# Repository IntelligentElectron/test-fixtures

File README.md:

# test-fixtures

Small, curated, **redistributable** EDA design files used as shared test fixtures
by IntelligentElectron's tooling. This repo is public and meant to be cloned /
submoduled by other repos' CI.

## Who uses it

- **[universal-netlist](https://github.com/IntelligentElectron/universal-netlist)** —
  consumes this repo as a git submodule at `test/fixtures` for parser/connectivity tests
  (Altium + Cadence today; KiCad parser in development).
- **[pcb-lens](https://github.com/IntelligentElectron/pcb-lens)** —
  consumes this repo as a git submodule at `test/fixtures`; runs
  `ipc2581/download-fixtures.sh` to fetch the IPC-2581 boards for layout tests.

## Layout

| Dir | Contents |
|-----|----------|
| `kicad/` | 13 KiCad projects, deliberately spanning **flat → deep hierarchy**, simple → complex, with **buses / global & hierarchical labels / power symbols** — chosen to exercise a KiCad parser. |
| `altium/` | Altium `.PrjPcb` / `.SchDoc` designs. |
| `cadence/` | Cadence Allegro / CIS designs (incl. exported `.dat` netlists). |
| `ipc2581/` | IPC-2581 PCB layout boards (RevA/B/C). Large XML downloaded on demand via `ipc2581/download-fixtures.sh` — not committed. |
| `NOTICE.md` | Upstream source, license, and copyright for every fixture. |

The `kicad/` set ranges from a single-sheet baseline (no hierarchy) up to 24-sheet,
depth-5 hierarchical designs with hundreds of bus connections — so a parser that
handles these handles the long tail.

## Using it from another repo

```sh
git submodule add https://github.com/IntelligentElectron/test-fixtures test/fixtures
git submodule update --init --remote      # pull latest fixtures
```

In CI (`actions/checkout`), set `submodules: true`. The repo is public, so the default
`GITHUB_TOKEN` can clone it — no extra credentials needed.

## Licensing

Every fixture is open-source / open-hardware (permissive or OSHW licenses) and is
**redistributable with attribution**; see `NOTICE.md`. If you are a copyright holder and
want your files removed, please open an issue.

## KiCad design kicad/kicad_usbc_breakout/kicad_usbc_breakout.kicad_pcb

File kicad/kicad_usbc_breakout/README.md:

# KiCad USB-C Breakout Board

Breaks out the USB 2.0 signals of a USB-C connector: VBUS, GND, D+, D- to pads
for soldering wires.

See the [schematic](kicad_usbc_breakout_schematic.pdf),
[pcb](kicad_usbc_breakout_pcb.pdf), and [BOM](usbc_breakout_BOM.csv).

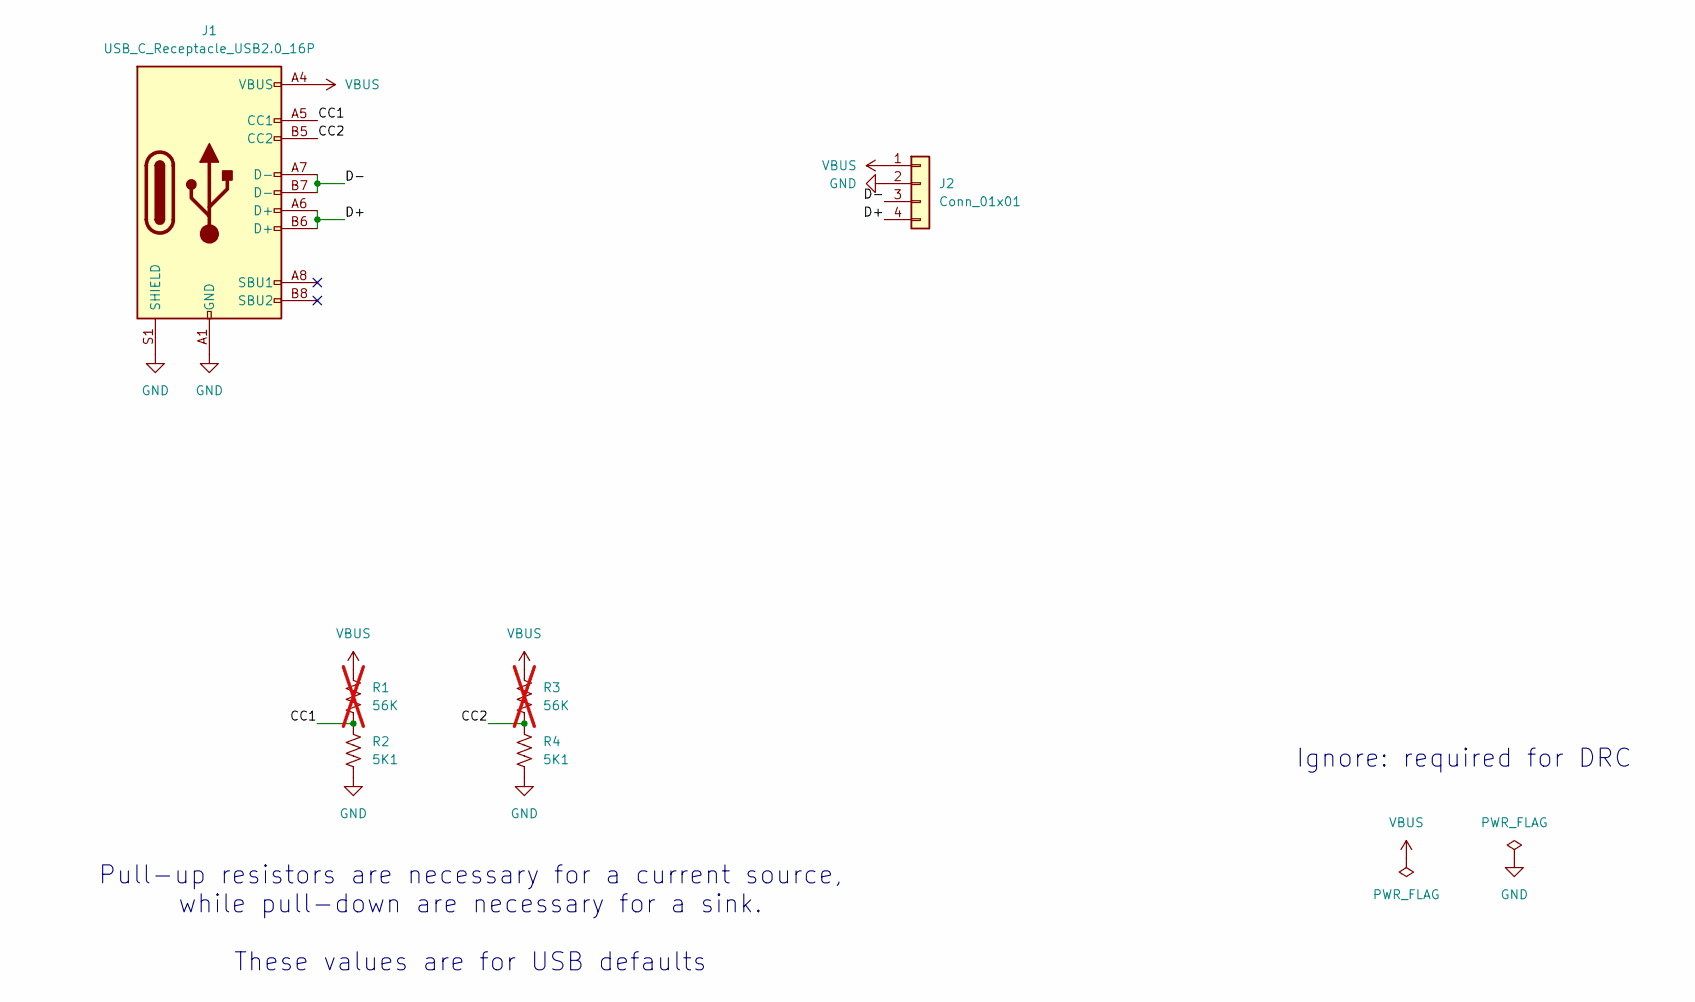
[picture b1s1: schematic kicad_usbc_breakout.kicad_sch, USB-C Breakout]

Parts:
J1: USB_C_Receptacle_USB2.0_16P; USB_C_Receptacle_GCT_USB4085_Reduced_Pad_Size; MFR Part Num USB4085-GF-A
J2: Conn_01x01; SolderWire-0.5sqmm_1x04_P4.8mm_D0.9mm_OD2.3mm_Relief
R1, R3: 56K; R_0805_2012Metric_Pad1.20x1.40mm_HandSolder; MFR Part Num CRCW080556K0FKEA; not fitted
R2, R4: 5K1; R_0805_2012Metric_Pad1.20x1.40mm_HandSolder; MFR Part Num CRCW08055K10FKEA

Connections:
/CC1: J1.A5 (CC1), R1.2, R2.1
/CC2: J1.B5 (CC2), R3.2, R4.1
/D+: J1.A6 (D+), J1.B6 (D+), J2.4
/D-: J1.A7 (D-), J1.B7 (D-), J2.3
GND: J1.A1 (GND), J1.A12 (GND), J1.B1 (GND), J1.B12 (GND), J1.S1 (SHIELD), J2.2, R2.2, R4.2
VBUS: J1.A4 (VBUS), J1.A9 (VBUS), J1.B4 (VBUS), J1.B9 (VBUS), J2.1, R1.1, R3.1

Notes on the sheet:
Pull-up resistors are necessary for a current source, while pull-down are necessary for a sink. These values are for USB defaults
Ignore: required for DRC

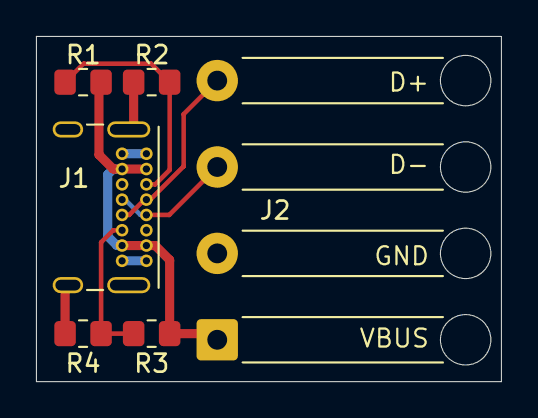
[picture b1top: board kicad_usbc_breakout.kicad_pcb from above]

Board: 2 copper layers, 25.8 x 19.2 mm, 6 parts (0 on the bottom side), 6 nets.

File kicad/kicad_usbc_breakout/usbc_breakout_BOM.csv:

"Reference","Value","Datasheet","Footprint","Qty","DNP","MFR","MFR Part Num"
"J1","USB_C_Receptacle_USB2.0_16P","https://www.usb.org/sites/default/files/documents/usb_type-c.zip","AAAA_Project_Library:USB_C_Receptacle_GCT_USB4085_Reduced_Pad_Size","1","","GCT","USB4085-GF-A"
"J2","Conn_01x01","~","Connector_Wire:SolderWire-0.5sqmm_1x04_P4.8mm_D0.9mm_OD2.3mm_Relief","1","","",""
"R1,R3","56K","~","Resistor_SMD:R_0805_2012Metric_Pad1.20x1.40mm_HandSolder","2","DNP","Vishay","CRCW080556K0FKEA"
"R2,R4","5K1","~","Resistor_SMD:R_0805_2012Metric_Pad1.20x1.40mm_HandSolder","2","","Vishay","CRCW08055K10FKEA"

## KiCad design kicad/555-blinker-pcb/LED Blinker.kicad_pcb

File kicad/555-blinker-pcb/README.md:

# LED Blinker Circuit with 555 Timer

This is a simple PCB designed in Kicad 7 for blinking an LED using an NA555P IC 555 timer. 

Below are screenshots of the PCB:

Schematics:

PCB Layout:

3D view of PCB:

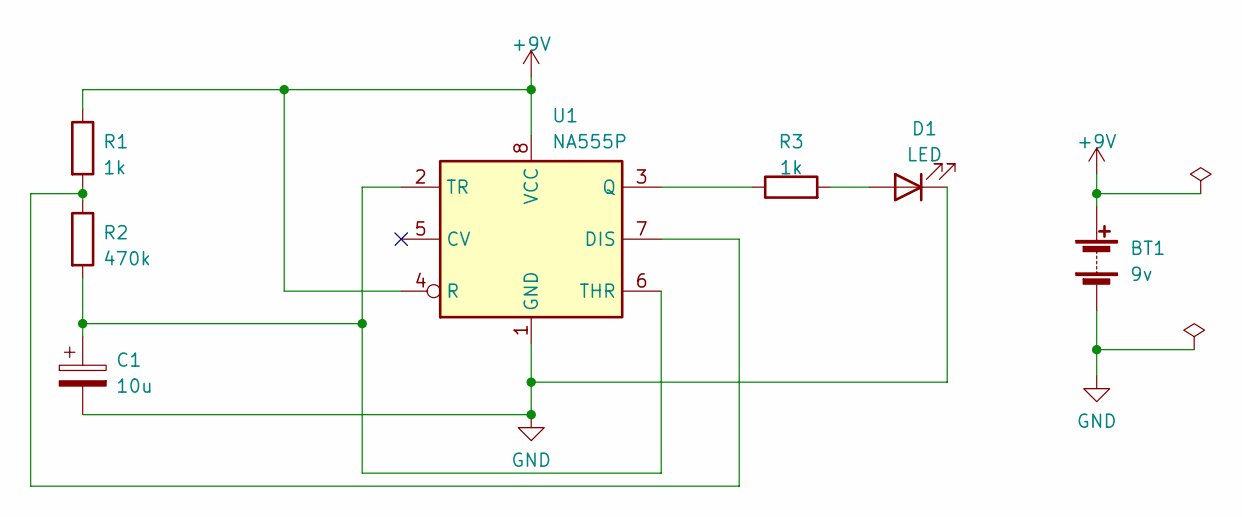
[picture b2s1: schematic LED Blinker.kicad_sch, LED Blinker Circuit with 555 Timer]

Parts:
BT1: 9v; TerminalBlock_bornier-2_P5.08mm
C1: 10u; CP_Axial_L10.0mm_D4.5mm_P15.00mm_Horizontal
D1: LED; LED_D8.0mm
R1, R3: 1k; R_Axial_DIN0204_L3.6mm_D1.6mm_P5.08mm_Horizontal
R2: 470k; R_Axial_DIN0204_L3.6mm_D1.6mm_P5.08mm_Horizontal
U1: NA555P; DIP-8_W7.62mm

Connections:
+9V: BT1.1 (+), R1.1, U1.4 (R), U1.8 (VCC)
GND: BT1.2 (-), C1.2, D1.1 (K), U1.1 (GND)
unnamed: D1.2 (A), R3.2
unnamed: R1.2, R2.1, U1.7 (DIS)
unnamed: R3.1, U1.3 (Q)
unnamed: C1.1, R2.2, U1.2 (TR), U1.6 (THR)

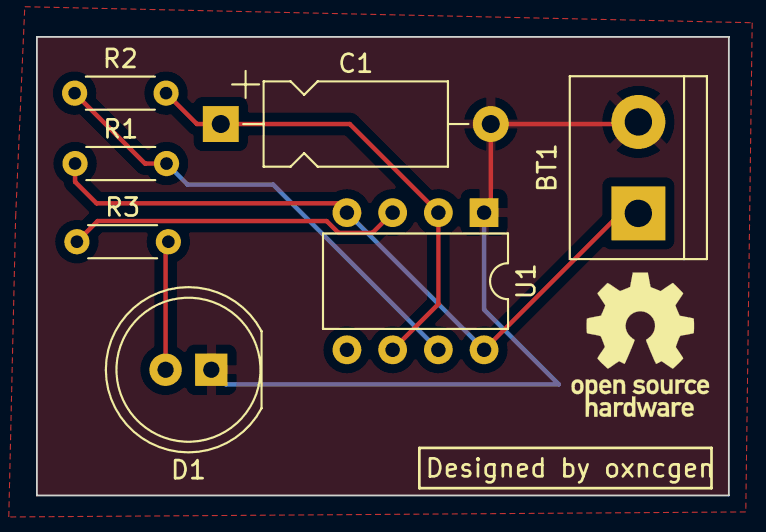
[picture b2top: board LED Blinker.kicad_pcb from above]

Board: 2 copper layers, 38.4 x 25.5 mm, 7 parts (0 on the bottom side), 6 nets.

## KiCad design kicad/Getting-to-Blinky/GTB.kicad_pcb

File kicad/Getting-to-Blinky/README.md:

# Getting To Blinky

In this project, I design a flashing LED circuit using a 555 timer. The purpose of this project is to familiarize myself with simple PCB design. The inspiration for this project comes from [Getting to Blinky 4.0](https://contextualelectronics.com/courses/getting-to-blinky/) for which I followed the tutorials in order to build my project.

## Getting Started

Simply clone the repo or download the .zip file.

### Prerequisites

To open any of the PCB design files, you will need Kicad.

### Installing

A step by step series of examples that tell you have to get a development env running

Installing Kicad

```
Kicad is free and open source and may be downloaded from http://kicad-pcb.org/download/
```

## Built With

* [Kicad](http://kicad-pcb.org/) - The PCB design software used

## Authors

* **Paul Natarajan** - *Hobbyist* - [Paul Natarajan](https://github.com/pdnataraj)
* **Contextual Electronics** - *Initial Work/Inspiration* - [Contextual Electronics](https://contextualelectronics.com/courses/getting-to-blinky/)

## License

This project is licensed under the MIT License - see the [LICENSE.md](LICENSE.md) file for details

## Acknowledgments

* Thank you Contextual Electronics for helping me take the first step towards PCB design.

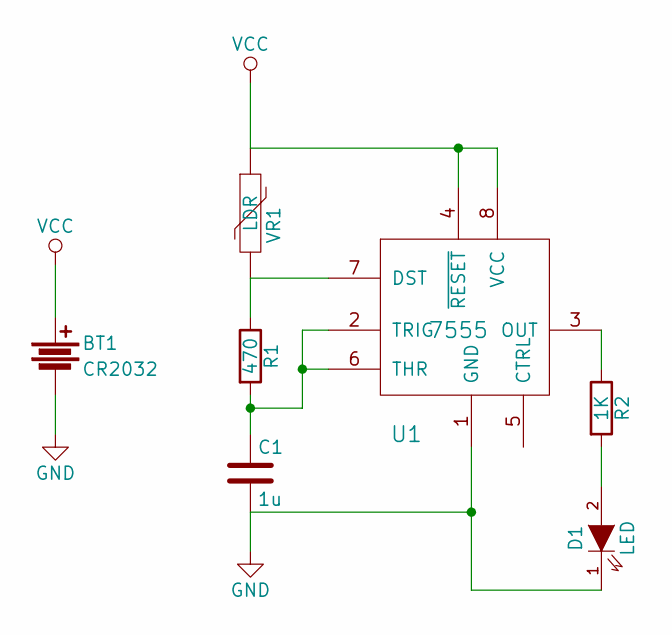
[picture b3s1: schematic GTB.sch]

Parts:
BT1: CR2032
C1: 1u; C_1206
D1: LED; LED_1206
R1: 470; R_1206
R2: 1K; R_1206
U1: 7555; SOIC-8-N
VR1: LDR; R1

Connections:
GND: BT1.2, C1.2, D1.1 (K), U1.1 (GND)
unnamed: C1.1, R1.2, U1.2 (TRIG), U1.6 (THR)
unnamed: D1.2 (A), R2.2
unnamed: R1.1, U1.7 (DST), VR1.2
unnamed: R2.1, U1.3 (OUT)
VCC: BT1.1, U1.4 (~RESET), U1.8 (VCC), VR1.1

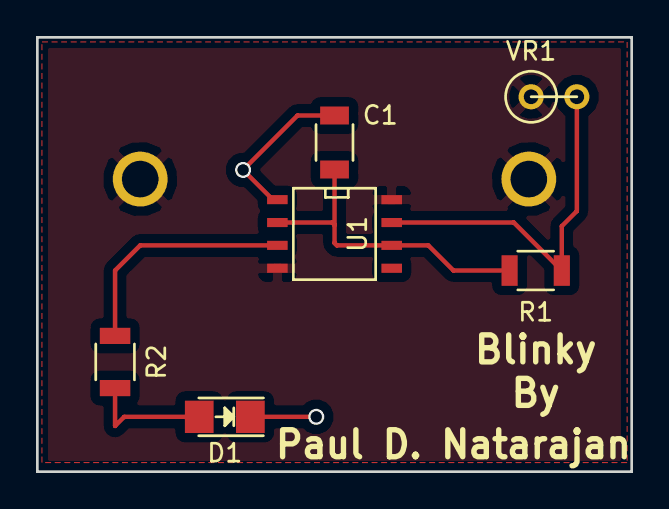
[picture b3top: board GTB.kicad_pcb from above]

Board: 2 copper layers, 33.0 x 24.1 mm, 7 parts (1 on the bottom side), 6 nets.

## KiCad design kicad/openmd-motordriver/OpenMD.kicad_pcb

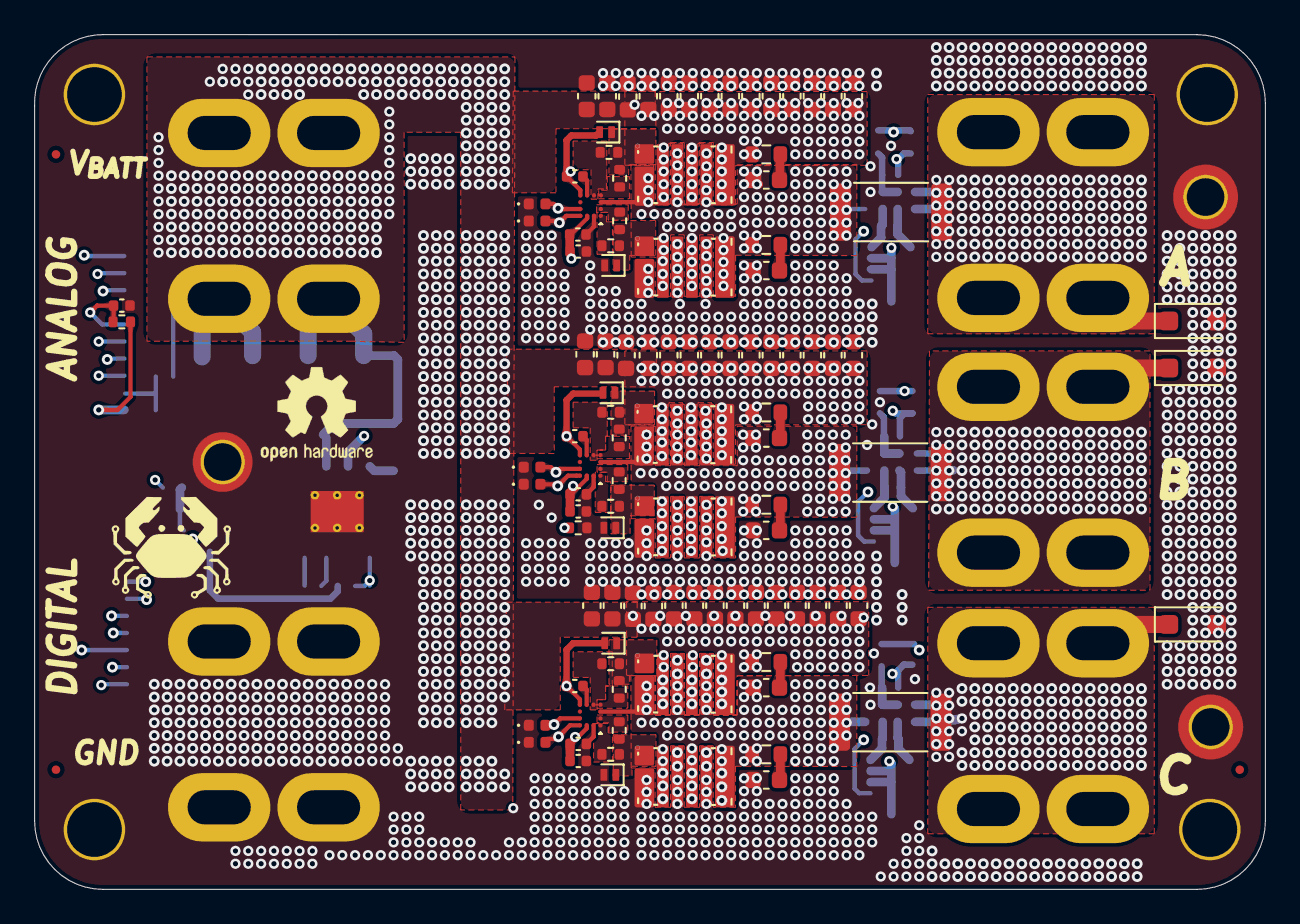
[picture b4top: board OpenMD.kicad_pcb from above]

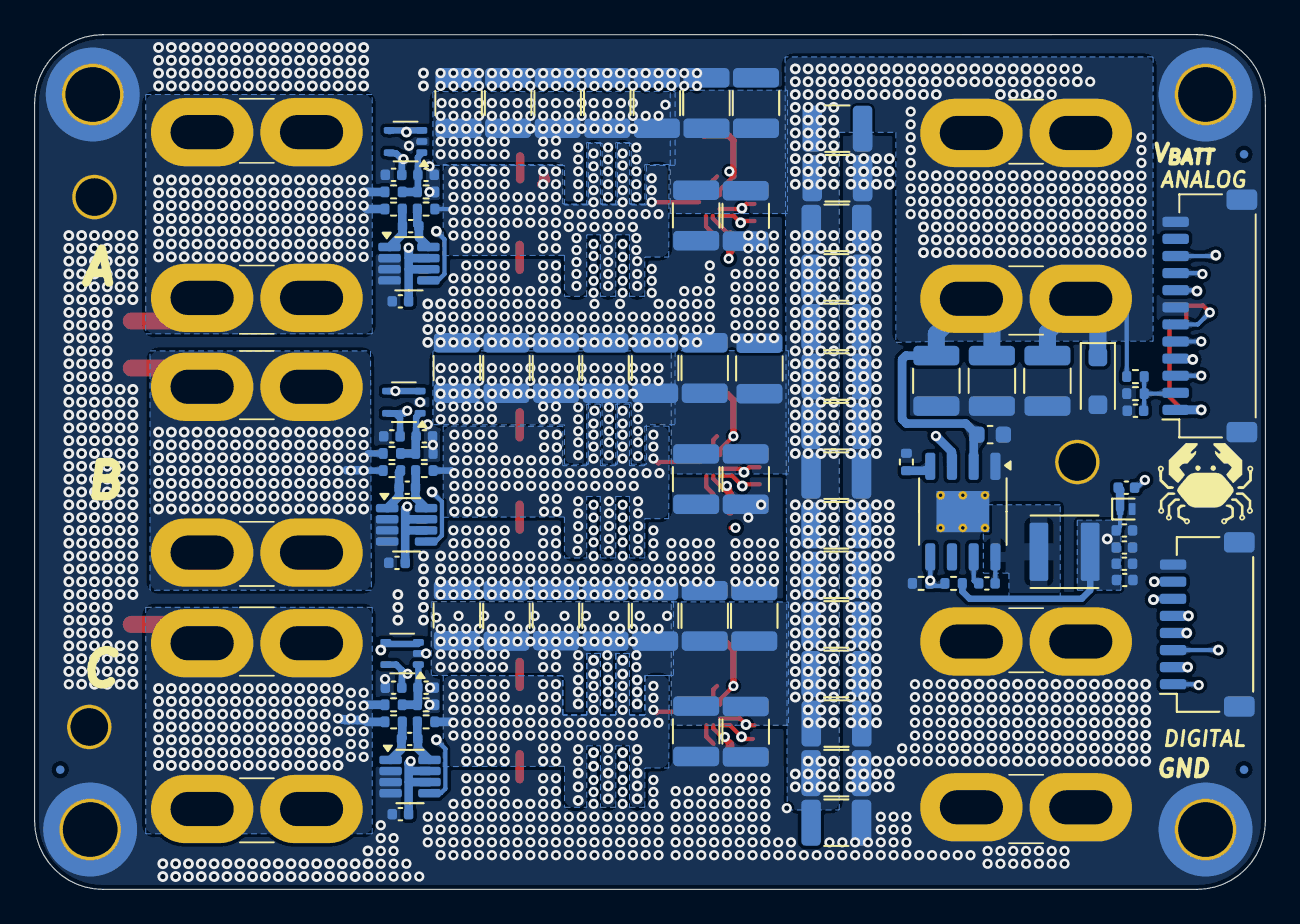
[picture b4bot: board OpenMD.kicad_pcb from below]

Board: 8 copper layers, 72.0 x 50.0 mm, 218 parts (106 on the bottom side), 65 nets.

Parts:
C1, C2, C3, C6, C7, C8, C9, C12, C15, C18, C19, C21, C23, C24, C26, C27, C28, C29, C31, C32, C34, C35, C78, C79, C80, C81, C82, C86, C87, C88, C89, C91, C93, C94, C98, C99, C100, C101, C102, C103, C104, C105, C106, C107, C108: 10uF; C_1210_3225Metric
C4, C5, C10, C13, C14, C16, C17, C20, C22, C25, C30, C33, C36, C46, C48, C50, C51, C53, C55, C58, C60, C62, C70, C71, C72, C73, C74, C75, C109, C110, C111, C112, C113, C114, C115, C116, C117, C118, C119, C120, C121, C122, C123: 100nF; C_0603_1608Metric
C11, C38, C39, C41, C42, C44, C45, C47, C52, C57, C63, C77: 100nF; C_0402_1005Metric
C37, C40, C43, C64, C65, C90: 4.7uF; C_0402_1005Metric
C49, C54, C59, C67, C68, C69, C95, C96, C97: 10nF; C_0402_1005Metric
C56, C61, C66, C83, C84, C85: C; C_0603_1608Metric
C76: 2.2nF; C_0402_1005Metric
C92: 20pF; C_0402_1005Metric
D7, D8, D9, D19: 100V; D_SOD-123F
D12, D13, D14, D15, D16, D17: 5V; D_0402_1005Metric
D18, D27, D28, D29, D30, D31, D32: 6V; D_SOD-882
FID1, FID2, FID3, FID4, FID5, FID6: Fiducial; Fiducial_0.5mm_Mask1mm
H1, H2, H3, H4: M3; MountingHole_3.2mm_M3_ISO14580_Pad_TopOnly
H5: M2; MountingHole_2.2mm_M2_ISO7380_Pad_TopOnly
H6, H7: M2; MountingHole_2.2mm_M2_DIN965_Pad_TopOnly
J1: GND; DIP-4_252
J2: Digital; JST_SH_SM08B-SRSS-TB_1x08-1MP_P1.00mm_Horizontal
J3: Analog; JST_SH_SM12B-SRSS-TB_1x12-1MP_P1.00mm_Horizontal
J5: A; DIP-4_252
J6: B; DIP-4_252
J7: C; DIP-4_252
J8: V_{MOTOR}; DIP-4_252
L1: 68uH; L_Abracon_ASPI-4030S
Q1, Q2, Q3, Q4, Q5, Q6: EPC2361; D0606F_100V
R1, R4, R6, R9, R11, R14: 1; R_0402_1005Metric
R2, R3, R7, R8, R12, R13: 0; R_0402_1005Metric
R5, R16, R18, R20, R32: 240k; R_0402_1005Metric
R10: 72k; R_0402_1005Metric
R15: 27k; R_0402_1005Metric
R17, R19, R21, R31, R34: 10k; R_0402_1005Metric
R22, R24, R25, R27, R28, R30: 10; R_0402_1005Metric
R23, R26, R29: .5m; R_2512_6332Metric
R38, R39, R40, R41, R42, R43: R; R_0603_1608Metric
SYM1: Logo_Open_Hardware_Large; OSHW-Logo2_7.3x6mm_SilkScreen
TH1: 10k NTC; R_0402_1005Metric
U1, U2, U3: LM1205; WLCSP1.6x1.6-12B_ECC
U4: LM5164DDA; HSOP-8-1EP_3.9x4.9mm_P1.27mm_EP2.41x3.1mm_ThermalVias
U5, U6, U7: OPA310xDCK; SOT-353_SC-70-5
U8, U9, U10: INA241A2; SOT-23-8

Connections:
/A: D7.1 (K), J5.1, R16.1, R23.2, R24.1
/AH: D27.1 (K), Q4.1 (G), R3.2, R4.2
/AL: D30.1 (K), Q1.1 (G), R1.2, R2.1
/B: D8.1 (K), J6.1, R18.1, R26.2, R27.1
/BH: D28.1 (K), Q5.1 (G), R8.2, R9.2
/BL: D31.1 (K), Q2.1 (G), R6.2, R7.1
/C: D9.1 (K), J7.1, R20.1, R29.2, R30.1
/CH: D29.1 (K), Q6.1 (G), R13.2, R14.2
/CL: D32.1 (K), Q3.1 (G), R11.2, R12.1
/DRV_TEMP_SENSE: C77.1, J3.6, R34.2, TH1.1
/ENABLE: J2.1, U4.3 (EN/UVLO)
/GND: C1.2, C2.2, C3.2, C4.2, C5.2, C6.2, C7.2, C8.2, C9.2, C10.2, C11.2, C12.2, C13.2, C14.2, C15.2, C16.2, C17.2, C18.2, C19.2, C20.2, C21.2, C22.2, C23.2, C24.2, C25.2, C26.2, C27.2, C28.2, C29.2, C30.2, C31.2, C32.2, C33.2, C34.2, C35.2, C36.2, C37.2, C38.2, C40.2, C41.2, C43.2, C44.2, C46.2, C47.2, C48.2, C50.2, C51.2, C52.2, C53.2, C55.2, C57.2, C58.2, C60.2, C62.2, C63.2, C64.2, C65.2, C67.2, C68.2, C69.2, C70.2, C71.2, C72.2, C73.2, C74.2, C75.2, C77.2, C78.2, C79.2, C80.2, C81.2, C82.2, C83.2, C84.2, C85.2, C86.2, C87.2, C88.2, C89.2, C90.2, C91.2, C93.2, C94.2, C95.2, C96.2, C97.2, C98.2, C99.2, C100.2, C101.2, C102.2, C103.2, C104.2, C105.2, C106.2, C107.2, C108.2, C109.2, C110.2, C111.2, C112.2, C113.2, C114.2, C115.2, C116.2, C117.2, C118.2, C119.2, C120.2, C121.2, C122.2, C123.2, D7.2 (A), D8.2 (A), D9.2 (A), D12.1 (A1), D13.1 (A1), D14.1 (A1), D15.1 (A1), D16.1 (A1), D17.1 (A1), D18.2 (A), D19.2 (A), D30.2 (A), D31.2 (A), D32.2 (A), H1.1, H2.1, H3.1, H4.1, H5.1, H6.1, H7.1, J1.1, J2.8, J2.MP (MountPin), J3.7, J3.12, J3.MP (MountPin), Q1.2 (S), Q1.4 (S), Q1.6 (S), Q2.2 (S), Q2.4 (S), Q2.6 (S), Q3.2 (S), Q3.4 (S), Q3.6 (S), R10.2, R15.2, R17.2, R19.2, R21.2, R31.2, TH1.2, U1.A2 (GND), U2.A2 (GND), U3.A2 (GND), U4.1 (GND), U4.9 (EP), U5.2 (V-), U6.2 (V-), U7.2 (V-), U8.2 (GND), U8.3 (REF2), U8.4 (GND), U9.2 (GND), U9.3 (REF2), U9.4 (GND), U10.2 (GND), U10.3 (REF2), U10.4 (GND)
/INPUT.AH: D12.2 (A2), J2.3, U1.B4 (HI)
/INPUT.AL: D15.2 (A2), J2.2, U1.A4 (LI)
/INPUT.BH: D13.2 (A2), J2.5, U2.B4 (HI)
/INPUT.BL: D16.2 (A2), J2.4, U2.A4 (LI)
/INPUT.CH: D14.2 (A2), J2.7, U3.B4 (HI)
/INPUT.CL: D17.2 (A2), J2.6, U3.A4 (LI)
/I_SENSE.A: J3.3, U8.5
/I_SENSE.B: J3.4, U9.5
/I_SENSE.C: J3.5, U10.5
/Phase Current Sensors/Current Sense A/V+: C49.1, R22.2, U8.8 (+)
/Phase Current Sensors/Current Sense A/V-: C49.2, R24.2, U8.1 (-)
/Phase Current Sensors/Current Sense B/V+: C54.1, R25.2, U9.8 (+)
/Phase Current Sensors/Current Sense B/V-: C54.2, R27.2, U9.1 (-)
/Phase Current Sensors/Current Sense C/V+: C59.1, R28.2, U10.8 (+)
/Phase Current Sensors/Current Sense C/V-: C59.2, R30.2, U10.1 (-)
/Predriver Voltage Supply/FB: C92.2, R5.2, R10.1, U4.5 (FB)
/Predriver Voltage Supply/SW: C76.2, L1.1, U4.8 (SW)
/Predrivers/Gate Driver A/BOOT: C39.1, U1.D3 (BOOT)
/Predrivers/Gate Driver A/LGH: R1.1, U1.B1 (LGH)
/Predrivers/Gate Driver A/LGL: R2.2, U1.A1 (LGL)
/Predrivers/Gate Driver A/UGH: R4.1, U1.D2 (UGH)
/Predrivers/Gate Driver A/UGL: R3.1, U1.D1 (UGL)
/Predrivers/Gate Driver B/BOOT: C42.1, U2.D3 (BOOT)
/Predrivers/Gate Driver B/LGH: R6.1, U2.B1 (LGH)
/Predrivers/Gate Driver B/LGL: R7.2, U2.A1 (LGL)
/Predrivers/Gate Driver B/UGH: R9.1, U2.D2 (UGH)
/Predrivers/Gate Driver B/UGL: R8.1, U2.D1 (UGL)
/Predrivers/Gate Driver C/BOOT: C45.1, U3.D3 (BOOT)
/Predrivers/Gate Driver C/LGH: R11.1, U3.B1 (LGH)
/Predrivers/Gate Driver C/LGL: R12.2, U3.A1 (LGL)
/Predrivers/Gate Driver C/UGH: R14.1, U3.D2 (UGH)
/Predrivers/Gate Driver C/UGL: R13.1, U3.D1 (UGL)
/SW.A: C39.2, C56.2, D27.2 (A), Q1.3 (D), Q1.5 (D), Q1.7 (D), Q4.2 (S), Q4.4 (S), Q4.6 (S), R22.1, R23.1, R41.1, U1.C1 (PHASE), U1.D4 (PHASE)
/SW.B: C42.2, C61.2, D28.2 (A), Q2.3 (D), Q2.5 (D), Q2.7 (D), Q5.2 (S), Q5.4 (S), Q5.6 (S), R25.1, R26.1, R42.1, U2.C1 (PHASE), U2.D4 (PHASE)
/SW.C: C45.2, C66.2, D29.2 (A), Q3.3 (D), Q3.5 (D), Q3.7 (D), Q6.2 (S), Q6.4 (S), Q6.6 (S), R28.1, R29.1, R43.1, U3.C1 (PHASE), U3.D4 (PHASE)
/V_SENSE: C63.1, J3.2, R31.1, R32.2
/V_SENSE.A: J3.8, U5.3 (-), U5.4
/V_SENSE.B: J3.9, U6.3 (-), U6.4
/V_SENSE.C: J3.10, U7.3 (-), U7.4
/V_{ANA}: C47.1, C52.1, C57.1, C95.1, C96.1, C97.1, J3.1, R34.1, U5.5 (V+), U6.5 (V+), U7.5 (V+), U8.6 (V+), U8.7 (REF1), U9.6 (V+), U9.7 (REF1), U10.6 (V+), U10.7 (REF1)
/V_{DRV}: C11.1, C37.1, C38.1, C40.1, C41.1, C43.1, C44.1, C64.1, C65.1, C90.1, C92.1, D18.1 (K), L1.2, R5.1, U1.A3 (VCC), U2.A3 (VCC), U3.A3 (VCC)
/V_{MOTOR}: C1.1, C2.1, C3.1, C4.1, C5.1, C6.1, C7.1, C8.1, C9.1, C10.1, C12.1, C13.1, C14.1, C15.1, C16.1, C17.1, C18.1, C19.1, C20.1, C21.1, C22.1, C23.1, C24.1, C25.1, C26.1, C27.1, C28.1, C29.1, C30.1, C31.1, C32.1, C33.1, C34.1, C35.1, C36.1, C46.1, C48.1, C50.1, C51.1, C53.1, C55.1, C58.1, C60.1, C62.1, C70.1, C71.1, C72.1, C73.1, C74.1, C75.1, C78.1, C79.1, C80.1, C81.1, C82.1, C86.1, C87.1, C88.1, C89.1, C91.1, C93.1, C94.1, C98.1, C99.1, C100.1, C101.1, C102.1, C103.1, C104.1, C105.1, C106.1, C107.1, C108.1, C109.1, C110.1, C111.1, C112.1, C113.1, C114.1, C115.1, C116.1, C117.1, C118.1, C119.1, C120.1, C121.1, C122.1, C123.1, D19.1 (K), J8.1, Q4.3 (D), Q4.5 (D), Q4.7 (D), Q5.3 (D), Q5.5 (D), Q5.7 (D), Q6.3 (D), Q6.5 (D), Q6.7 (D), R32.1, R38.1, R39.1, R40.1, U4.2 (VIN)
unnamed: C56.1, R38.2
unnamed: C61.1, R39.2
unnamed: C66.1, R40.2
unnamed: C83.1, R41.2
unnamed: C84.1, R42.2
unnamed: C85.1, R43.2
unnamed: C76.1, U4.7 (BST)
unnamed: R15.1, U4.4 (RON)
unnamed: C67.1, R16.2, R17.1, U5.1 (+)
unnamed: C68.1, R18.2, R19.1, U6.1 (+)
unnamed: C69.1, R20.2, R21.1, U7.1 (+)

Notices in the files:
kicad/modular-synth-vco/main_VCO_board.kicad_pcb:
creativecommons.org/licenses/by/4.0
licence: CC by 4.0
kicad/openmd-motordriver/OpenMD.kicad_pcb:
License: CERN-OHL-W-2.0
